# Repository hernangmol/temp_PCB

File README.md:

# temp_PCB
Repositorio temporal de diseños PCB propios

Carpeta SMTB:

Contiene el trabajo "Sistema de monitoreo térmico de bogies", realizado en el marco de la Especialización en Sistemas Embebidos (FIUBA) para Trenes Argentinos Operaciones.
Se trata de un desarrollo para sustitución de importación de un sistema incluido en el equipamiento original de las locomotoras CNR - CKD 8G/H.
(Ver repositorio github/hernangmol/SMTB.git)

Carpeta Barra_cortocircuito:

Se trata del desarrollo realizado en CENADIF de una barra de cortocircuito para tercer riel. La misma mantiene la condición segura mientras se realizan tareas de mantenimiento de tercer riel.
Incorpora además un detector de tensión y luces de aviso de riel energizado.

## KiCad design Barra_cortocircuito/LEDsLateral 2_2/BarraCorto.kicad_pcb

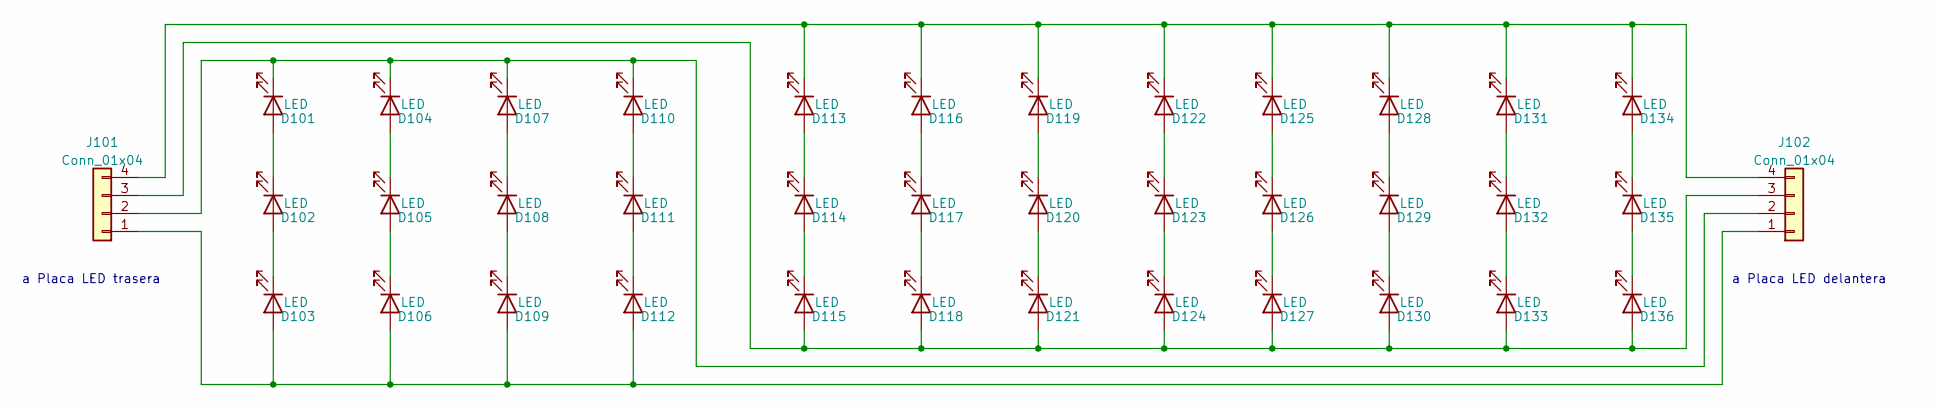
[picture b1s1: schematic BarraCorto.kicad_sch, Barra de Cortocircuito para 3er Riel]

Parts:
D101, D102, D103, D104, D105, D106, D107, D108, D109, D110, D111, D112, D113, D114, D115, D116, D117, D118, D119, D120, D121, D122, D123, D124, D125, D126, D127, D128, D129, D130, D131, D132, D133, D134, D135, D136: LED; LED_PLCC_2835
J101, J102: Conn_01x04; molex_EDGELOCK_4-CKT_Mod

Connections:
unnamed: D101.1 (K), D104.1 (K), D107.1 (K), D110.1 (K), J101.2, J102.2
unnamed: D101.2 (A), D102.1 (K)
unnamed: D102.2 (A), D103.1 (K)
unnamed: D103.2 (A), D106.2 (A), D109.2 (A), D112.2 (A), J101.1, J102.1
unnamed: D104.2 (A), D105.1 (K)
unnamed: D105.2 (A), D106.1 (K)
unnamed: D107.2 (A), D108.1 (K)
unnamed: D108.2 (A), D109.1 (K)
unnamed: D110.2 (A), D111.1 (K)
unnamed: D111.2 (A), D112.1 (K)
unnamed: D113.1 (K), D116.1 (K), D119.1 (K), D122.1 (K), D125.1 (K), D128.1 (K), D131.1 (K), D134.1 (K), J101.4, J102.4
unnamed: D113.2 (A), D114.1 (K)
unnamed: D114.2 (A), D115.1 (K)
unnamed: D115.2 (A), D118.2 (A), D121.2 (A), D124.2 (A), D127.2 (A), D130.2 (A), D133.2 (A), D136.2 (A), J101.3, J102.3
unnamed: D116.2 (A), D117.1 (K)
unnamed: D117.2 (A), D118.1 (K)
unnamed: D119.2 (A), D120.1 (K)
unnamed: D120.2 (A), D121.1 (K)
unnamed: D122.2 (A), D123.1 (K)
unnamed: D123.2 (A), D124.1 (K)
unnamed: D125.2 (A), D126.1 (K)
unnamed: D126.2 (A), D127.1 (K)
unnamed: D128.2 (A), D129.1 (K)
unnamed: D129.2 (A), D130.1 (K)
unnamed: D131.2 (A), D132.1 (K)
unnamed: D132.2 (A), D133.1 (K)
unnamed: D134.2 (A), D135.1 (K)
unnamed: D135.2 (A), D136.1 (K)

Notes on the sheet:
a Placa LED delantera
a Placa LED trasera

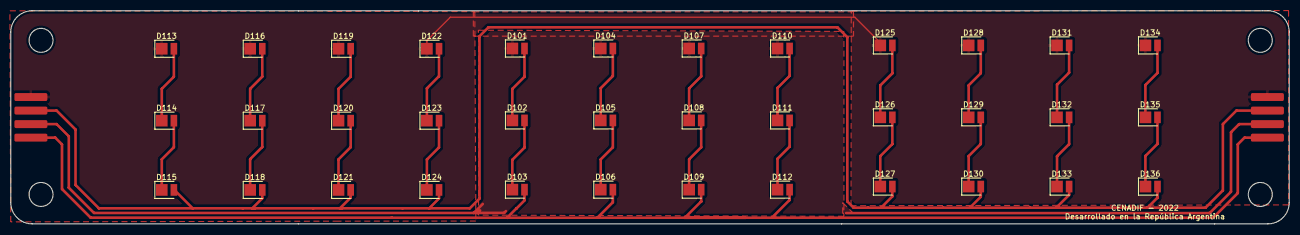
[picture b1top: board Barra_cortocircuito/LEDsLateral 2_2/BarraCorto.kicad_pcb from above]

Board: 2 copper layers, 240.0 x 40.0 mm, 38 parts (0 on the bottom side), 28 nets.

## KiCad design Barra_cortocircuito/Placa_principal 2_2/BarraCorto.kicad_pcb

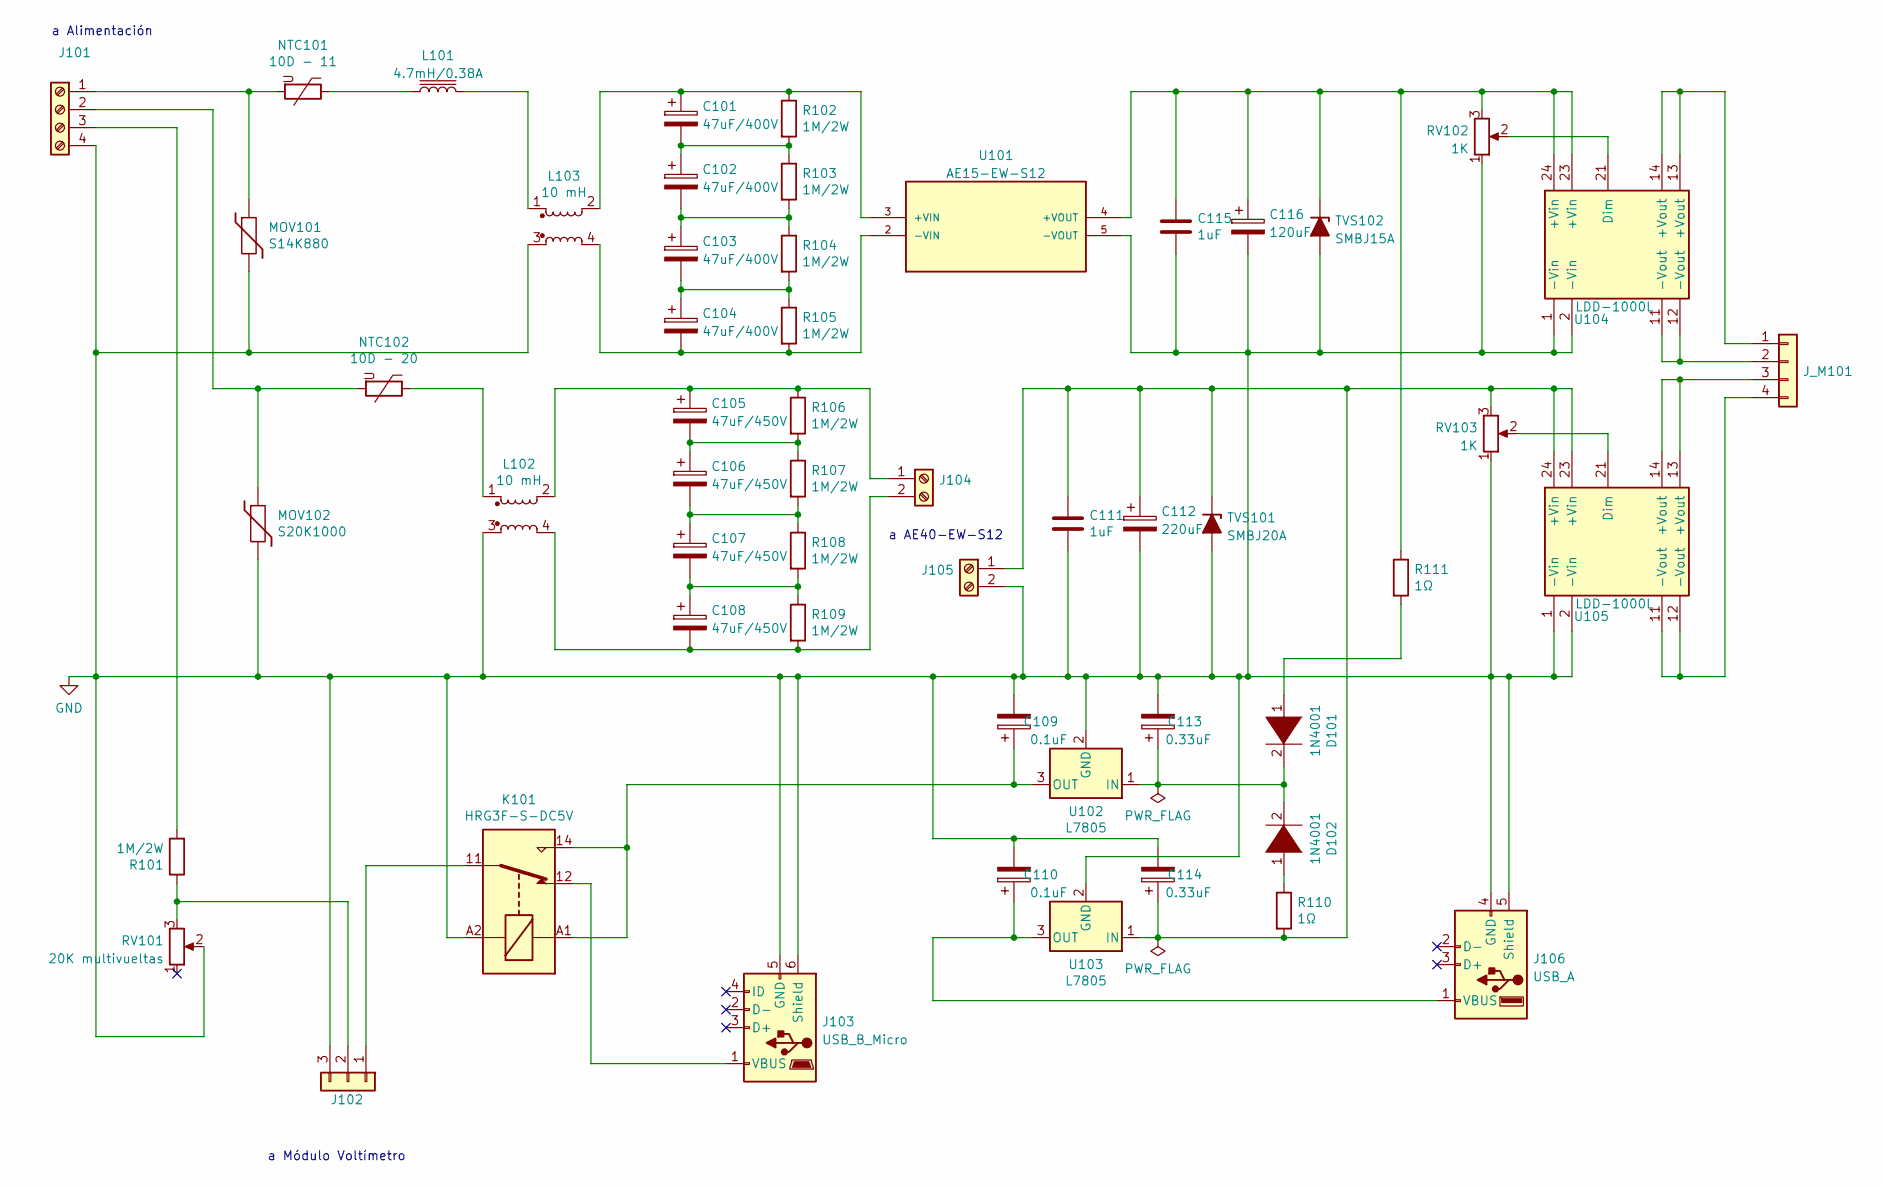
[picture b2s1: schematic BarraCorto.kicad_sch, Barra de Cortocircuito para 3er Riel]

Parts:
C101, C102, C103, C104: 47uF/400V; CP_Radial_D18.0mm_P7.50mm
C105, C106, C107, C108: 47uF/450V; CP_Radial_D18.0mm_P7.50mm
C109, C110: 0.1uF; CP_Radial_D8.0mm_P5.00mm
C111, C115: 1uF; C_Disc_D8.0mm_W2.5mm_P5.00mm
C112: 220uF; CP_Radial_D18.0mm_P7.50mm
C113, C114: 0.33uF; CP_Radial_D8.0mm_P5.00mm
C116: 120uF; CP_Radial_D18.0mm_P7.50mm
D101, D102: 1N4001; D_DO-41_SOD81_P10.16mm_Horizontal
J101: Bornera_Tornillo_01x04; TerminalBlock_bornier-4_P5.08mm
J102: Conn_01x03; Molex_KK-254_AE-6410-03A_1x03_P2.54mm_Vertical
J103: USB_B_Micro; PinHeader_1x06_P2.54mm_Vertical
J104, J105: BorneraTornillo_01x02; TerminalBlock_bornier-2_P5.08mm
J106: USB_A; USB_A_Molex_67643_Horizontal
J_M101: Conn_01x04; Molex_KK-254_AE-6410-04A_1x04_P2.54mm_Vertical
K101: HRG3F-S-DC5V
L101: 4.7mH/0.38A; L_Radial_D27.9mm_P19.05mm_Vishay_IHB-3
L102, L103: 10 mH
MOV101: S14K880; RV_Disc_D15.5mm_W11mm_P7.5mm
MOV102: S20K1000; RV_Disc_D21.5mm_W11.4mm_P10mm
NTC101: 10D - 11; RV_Disc_D12mm_W7.9mm_P7.5mm
NTC102: 10D - 20; RV_Disc_D21.5mm_W7.1mm_P10mm
R101, R102, R103, R104, R105, R106, R107, R108, R109: 1M/2W; R_Axial_DIN0516_L15.5mm_D5.0mm_P20.32mm_Horizontal
R110, R111: 1Ω; R_Axial_DIN0516_L15.5mm_D5.0mm_P20.32mm_Horizontal
RV101: 20K multivueltas; Potentiometer_Bourns_3296W_Vertical
RV102, RV103: 1K; Potentiometer_Bourns_3296W_Vertical
TVS101: SMBJ20A; D_SMB
TVS102: SMBJ15A; D_SMB
U101: AE15-EW-S12; AE15_EW_S12; PARTREV 1.0
U102, U103: L7805; TO-220-3_Horizontal_TabDown
U104, U105: LDD-1000L

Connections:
GND: C109.2, C110.2, C111.2, C112.2, C113.2, C114.2, C115.2, C116.2, J101.4, J102.3, J103.5 (GND), J103.6 (Shield), J105.2, J106.4 (GND), J106.5 (Shield), K101.A2, L102.3, L103.3, MOV101.2, MOV102.2, RV101.2, RV102.1, RV103.1, TVS101.2 (A), TVS102.2 (A), U101.5 (-VOUT), U102.2 (GND), U103.2 (GND), U104.1 (-Vin), U104.2 (-Vin), U105.1 (-Vin), U105.2 (-Vin)
unnamed: C101.1, L103.2, R102.1, U101.3 (+VIN)
unnamed: C101.2, C102.1, R102.2, R103.1
unnamed: C102.2, C103.1, R103.2, R104.1
unnamed: C103.2, C104.1, R104.2, R105.1
unnamed: C104.2, L103.4, R105.2, U101.2 (-VIN)
unnamed: C105.1, J104.1, L102.2, R106.1
unnamed: C105.2, C106.1, R106.2, R107.1
unnamed: C106.2, C107.1, R107.2, R108.1
unnamed: C107.2, C108.1, R108.2, R109.1
unnamed: C108.2, J104.2, L102.4, R109.2
unnamed: C109.1, K101.14, K101.A1, U102.3 (OUT)
unnamed: C110.1, J106.1 (VBUS), U103.3 (OUT)
unnamed: C111.1, C112.1, C114.1, J105.1, R110.2, RV103.3, TVS101.1 (K), U103.1 (IN), U105.23 (+Vin), U105.24 (+Vin)
unnamed: C113.1, D101.2 (A), D102.2 (A), U102.1 (IN)
unnamed: C115.1, C116.1, R111.1, RV102.3, TVS102.1 (K), U101.4 (+VOUT), U104.23 (+Vin), U104.24 (+Vin)
unnamed: D101.1 (K), R111.2
unnamed: D102.1 (K), R110.1
unnamed: J101.1, MOV101.1, NTC101.2
unnamed: J101.2, MOV102.1, NTC102.2
unnamed: J101.3, R101.2
unnamed: J102.1, K101.11
unnamed: J102.2, R101.1, RV101.3
unnamed: J103.1 (VBUS), K101.12
unnamed: J_M101.1, U104.13 (+Vout), U104.14 (+Vout)
unnamed: J_M101.2, U104.11 (-Vout), U104.12 (-Vout)
unnamed: J_M101.3, U105.13 (+Vout), U105.14 (+Vout)
unnamed: J_M101.4, U105.11 (-Vout), U105.12 (-Vout)
unnamed: L101.1, NTC101.1
unnamed: L101.2, L103.1
unnamed: L102.1, NTC102.1
unnamed: RV102.2, U104.21 (Dim)
unnamed: RV103.2, U105.21 (Dim)

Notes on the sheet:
a AE40-EW-S12
a Módulo Voltímetro
a Alimentación

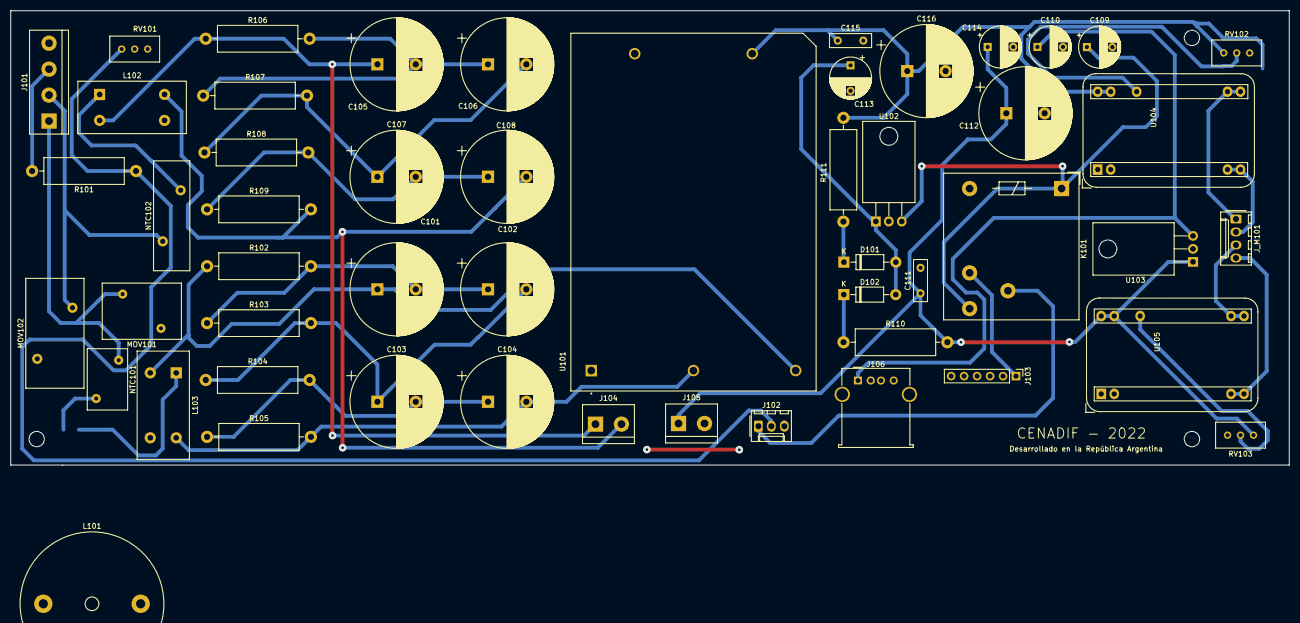
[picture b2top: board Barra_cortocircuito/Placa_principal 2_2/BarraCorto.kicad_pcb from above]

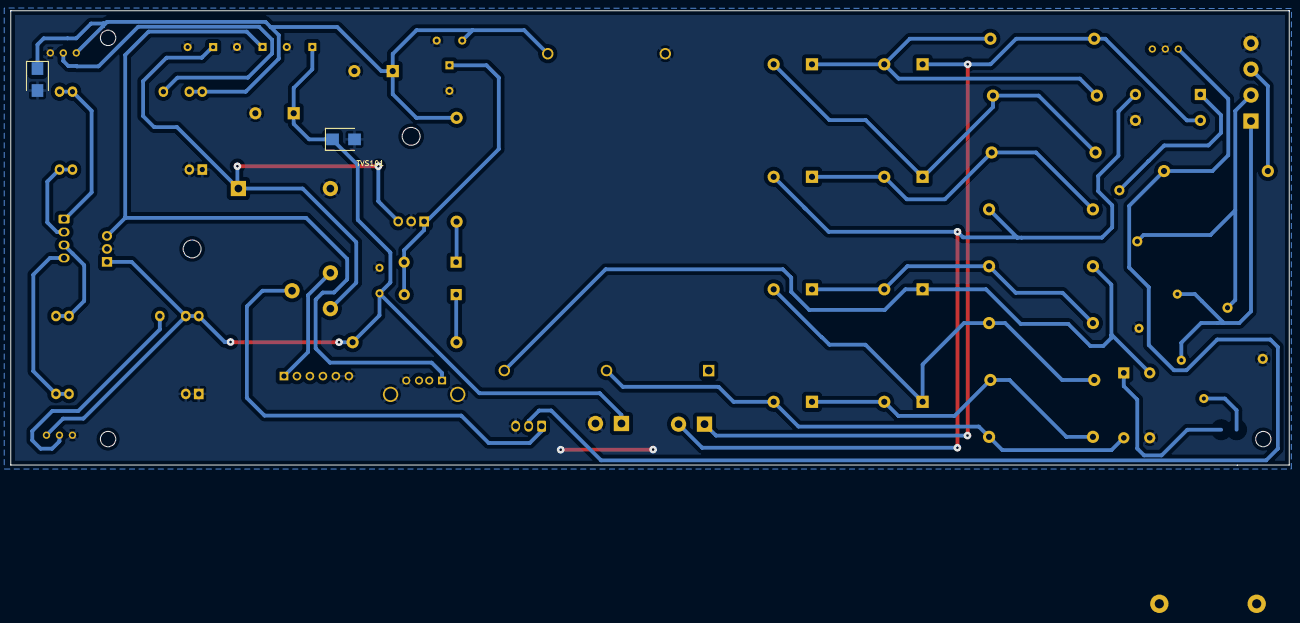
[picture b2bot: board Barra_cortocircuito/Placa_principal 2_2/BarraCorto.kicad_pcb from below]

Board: 2 copper layers, 250.2 x 88.9 mm, 54 parts (2 on the bottom side), 33 nets.

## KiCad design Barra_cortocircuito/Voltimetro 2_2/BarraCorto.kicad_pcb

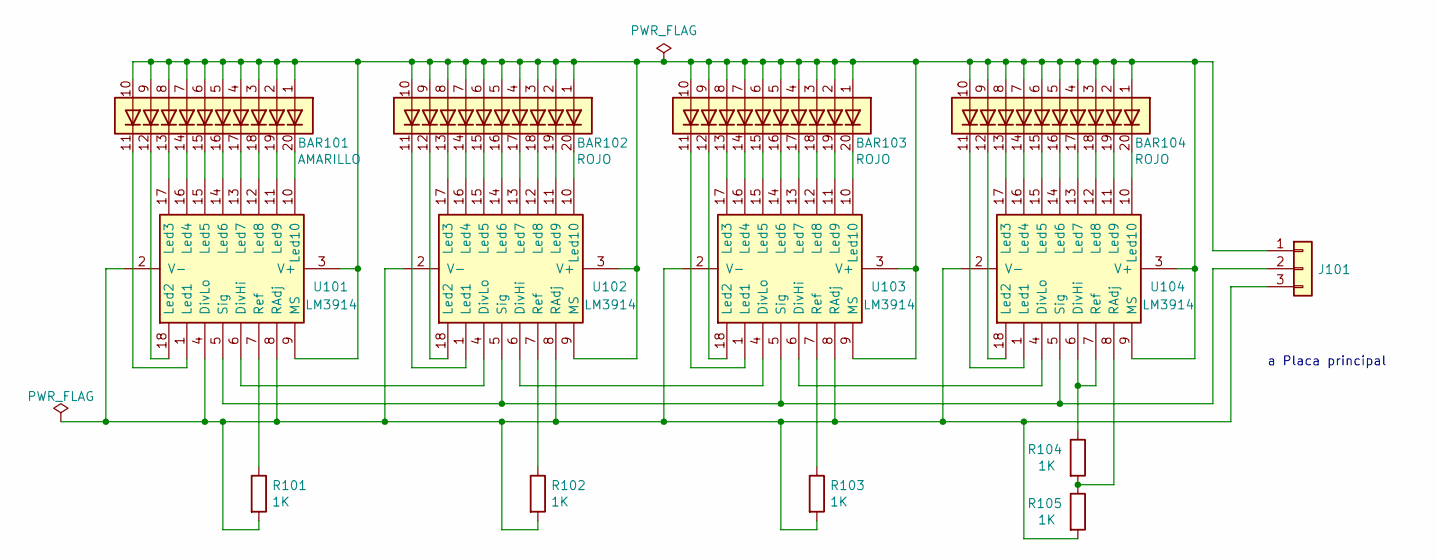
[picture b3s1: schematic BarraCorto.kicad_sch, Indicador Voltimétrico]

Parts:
BAR101: AMARILLO; HDSP-4830
BAR102, BAR103, BAR104: ROJO; HDSP-4830
J101: Conn_01x03; Molex_KK-254_AE-6410-03A_1x03_P2.54mm_Vertical
R101, R102, R103, R104, R105: 1K; R_Axial_DIN0207_L6.3mm_D2.5mm_P10.16mm_Horizontal
U101, U102, U103, U104: LM3914; DIP-18_W7.62mm_Socket

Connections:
unnamed: BAR101.1 (A), BAR101.2 (A), BAR101.3 (A), BAR101.4 (A), BAR101.5 (A), BAR101.6 (A), BAR101.7 (A), BAR101.8 (A), BAR101.9 (A), BAR101.10 (A), BAR102.1 (A), BAR102.2 (A), BAR102.3 (A), BAR102.4 (A), BAR102.5 (A), BAR102.6 (A), BAR102.7 (A), BAR102.8 (A), BAR102.9 (A), BAR102.10 (A), BAR103.1 (A), BAR103.2 (A), BAR103.3 (A), BAR103.4 (A), BAR103.5 (A), BAR103.6 (A), BAR103.7 (A), BAR103.8 (A), BAR103.9 (A), BAR103.10 (A), BAR104.1 (A), BAR104.2 (A), BAR104.3 (A), BAR104.4 (A), BAR104.5 (A), BAR104.6 (A), BAR104.7 (A), BAR104.8 (A), BAR104.9 (A), BAR104.10 (A), J101.1, U101.3 (V+), U101.9 (MS), U102.3 (V+), U102.9 (MS), U103.3 (V+), U103.9 (MS), U104.3 (V+), U104.9 (MS)
unnamed: BAR101.11 (K), U101.1 (Led1)
unnamed: BAR101.12 (K), U101.18 (Led2)
unnamed: BAR101.13 (K), U101.17 (Led3)
unnamed: BAR101.14 (K), U101.16 (Led4)
unnamed: BAR101.15 (K), U101.15 (Led5)
unnamed: BAR101.16 (K), U101.14 (Led6)
unnamed: BAR101.17 (K), U101.13 (Led7)
unnamed: BAR101.18 (K), U101.12 (Led8)
unnamed: BAR101.19 (K), U101.11 (Led9)
unnamed: BAR101.20 (K), U101.10 (Led10)
unnamed: BAR102.11 (K), U102.1 (Led1)
unnamed: BAR102.12 (K), U102.18 (Led2)
unnamed: BAR102.13 (K), U102.17 (Led3)
unnamed: BAR102.14 (K), U102.16 (Led4)
unnamed: BAR102.15 (K), U102.15 (Led5)
unnamed: BAR102.16 (K), U102.14 (Led6)
unnamed: BAR102.17 (K), U102.13 (Led7)
unnamed: BAR102.18 (K), U102.12 (Led8)
unnamed: BAR102.19 (K), U102.11 (Led9)
unnamed: BAR102.20 (K), U102.10 (Led10)
unnamed: BAR103.11 (K), U103.1 (Led1)
unnamed: BAR103.12 (K), U103.18 (Led2)
unnamed: BAR103.13 (K), U103.17 (Led3)
unnamed: BAR103.14 (K), U103.16 (Led4)
unnamed: BAR103.15 (K), U103.15 (Led5)
unnamed: BAR103.16 (K), U103.14 (Led6)
unnamed: BAR103.17 (K), U103.13 (Led7)
unnamed: BAR103.18 (K), U103.12 (Led8)
unnamed: BAR103.19 (K), U103.11 (Led9)
unnamed: BAR103.20 (K), U103.10 (Led10)
unnamed: BAR104.11 (K), U104.1 (Led1)
unnamed: BAR104.12 (K), U104.18 (Led2)
unnamed: BAR104.13 (K), U104.17 (Led3)
unnamed: BAR104.14 (K), U104.16 (Led4)
unnamed: BAR104.15 (K), U104.15 (Led5)
unnamed: BAR104.16 (K), U104.14 (Led6)
unnamed: BAR104.17 (K), U104.13 (Led7)
unnamed: BAR104.18 (K), U104.12 (Led8)
unnamed: BAR104.19 (K), U104.11 (Led9)
unnamed: BAR104.20 (K), U104.10 (Led10)
unnamed: J101.2, U101.5 (Sig), U102.5 (Sig), U103.5 (Sig), U104.5 (Sig)
unnamed: J101.3, R101.2, R102.2, R103.2, R105.2, U101.2 (V-), U101.4 (DivLo), U101.8 (RAdj), U102.2 (V-), U102.8 (RAdj), U103.2 (V-), U103.8 (RAdj), U104.2 (V-)
unnamed: R101.1, U101.7 (Ref)
unnamed: R102.1, U102.7 (Ref)
unnamed: R103.1, U103.7 (Ref)
unnamed: R104.1, U104.6 (DivHi), U104.7 (Ref)
unnamed: R104.2, R105.1, U104.8 (RAdj)
unnamed: U101.6 (DivHi), U102.4 (DivLo)
unnamed: U102.6 (DivHi), U103.4 (DivLo)
unnamed: U103.6 (DivHi), U104.4 (DivLo)

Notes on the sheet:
a Placa principal

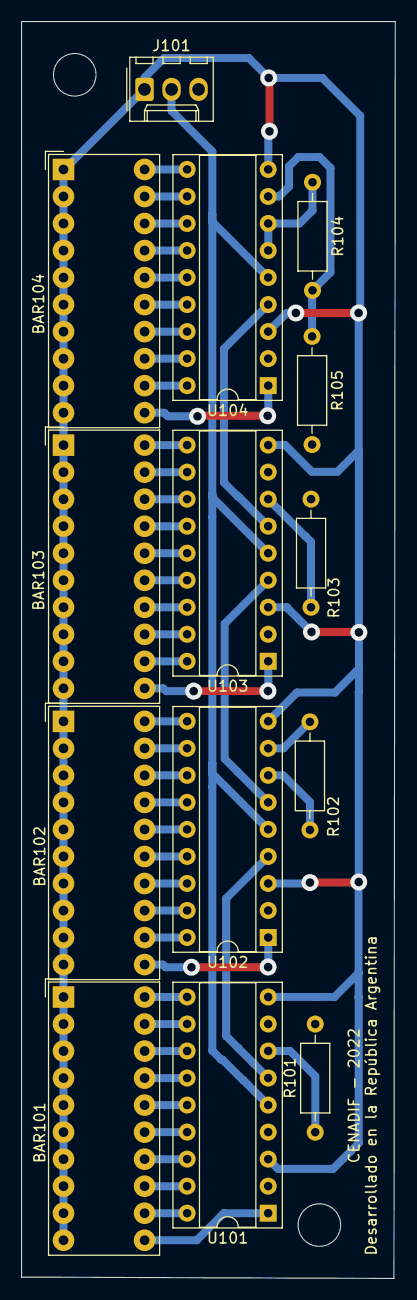
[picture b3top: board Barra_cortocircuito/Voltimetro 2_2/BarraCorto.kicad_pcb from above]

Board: 2 copper layers, 35.1 x 118.1 mm, 14 parts (0 on the bottom side), 51 nets.

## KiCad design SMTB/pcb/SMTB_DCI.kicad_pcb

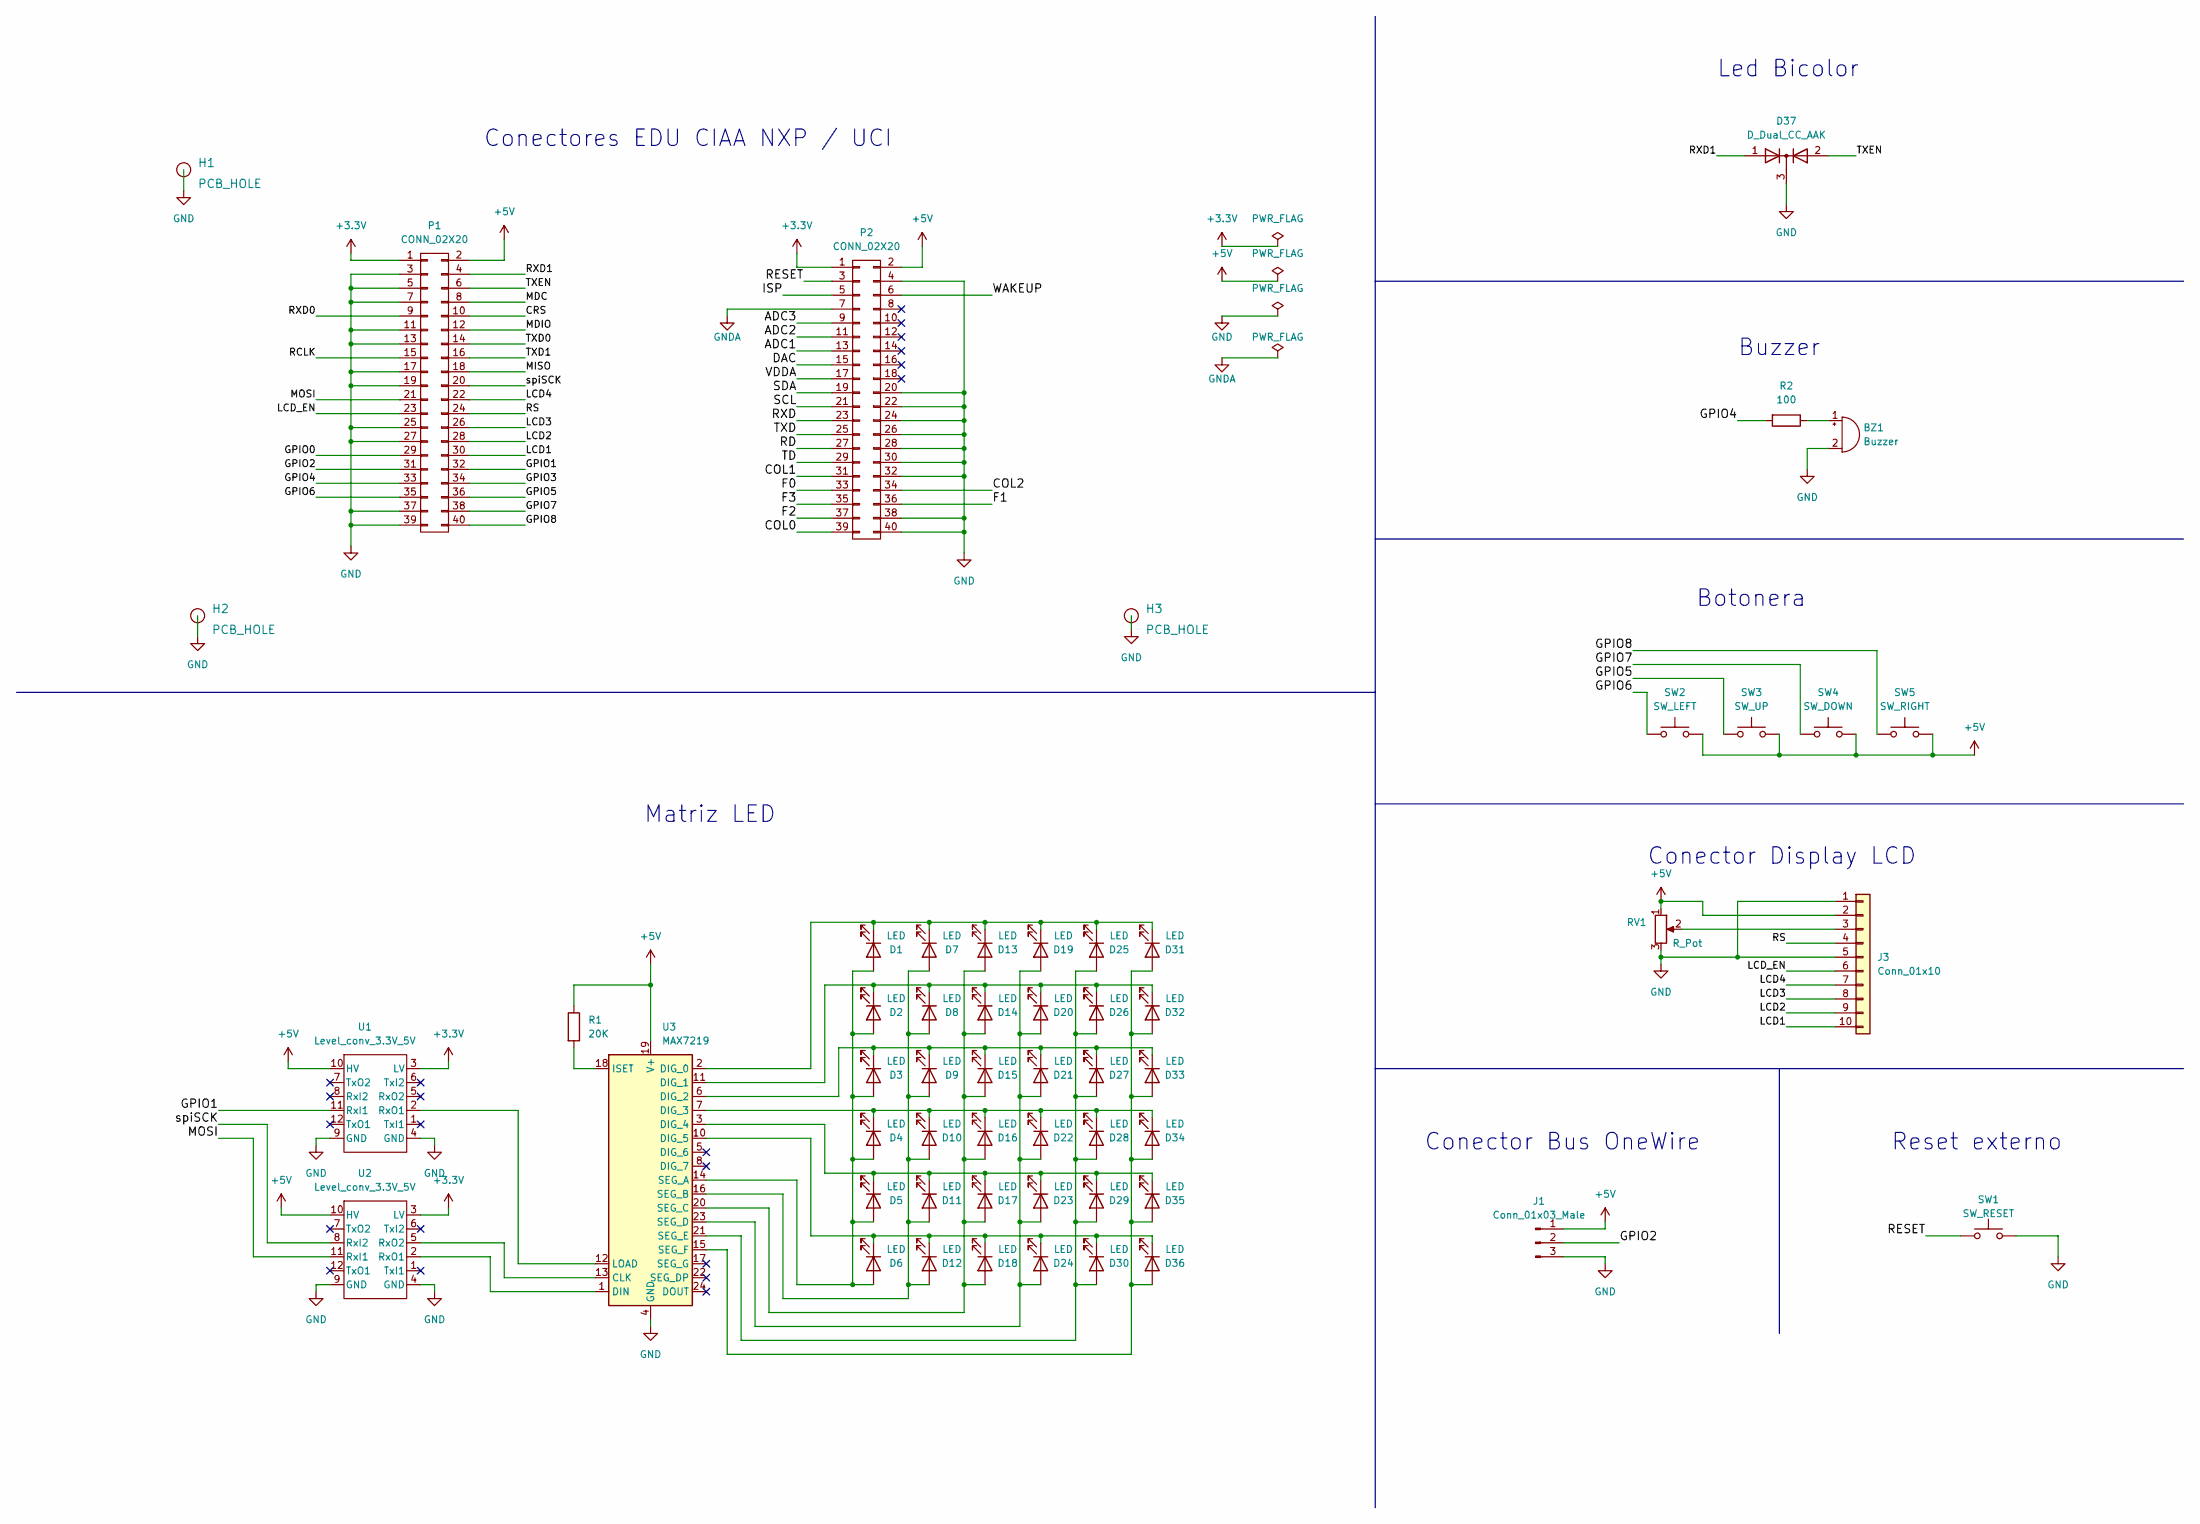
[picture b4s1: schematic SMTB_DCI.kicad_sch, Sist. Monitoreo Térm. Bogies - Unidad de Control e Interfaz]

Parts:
BZ1: Buzzer; Buzzer_12x9.5RM7.6
D1, D2, D3, D4, D5, D6, D7, D8, D9, D10, D11, D12, D13, D14, D15, D16, D17, D18, D19, D20, D21, D22, D23, D24, D25, D26, D27, D28, D29, D30, D31, D32, D33, D34, D35, D36: LED; LED_D5.0mm
D37: D_Dual_CC_AAK; LED_D5.0mm-3
H1: PCB_HOLE
H2, H3: PCB_HOLE; MountingHole_4.3mm_M4_ISO14580_Pad_TopBottom
J1: Conn_01x03_Male; Molex_KK-254_AE-6410-03A_1x03_P2.54mm_Vertical
J3: Conn_01x10; Molex_KK-254_AE-6410-10A_1x10_P2.54mm_Vertical
P1, P2: CONN_02X20; PinHeader_2x20_P2.54mm_Vertical
R1: 20K; R_Axial_DIN0207_L6.3mm_D2.5mm_P10.16mm_Horizontal
R2: 100; R_Axial_DIN0207_L6.3mm_D2.5mm_P10.16mm_Horizontal
RV1: R_Pot; Potentiometer_Bourns_3296W_Vertical
SW1: SW_RESET; SW_PUSH_6mm
SW2: SW_LEFT; SW_PUSH_6mm
SW3: SW_UP; SW_PUSH_6mm
SW4: SW_DOWN; SW_PUSH_6mm
SW5: SW_RIGHT; SW_PUSH_6mm
U1, U2: Level_conv_3.3V_5V; Conv_DCDC
U3: MAX7219; DIP-24_W7.62mm

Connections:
+3.3V: P1.1, P2.1, U1.3 (LV), U2.3 (LV)
+5V: J1.1, J3.2, P1.2, P2.2, R1.1, RV1.1, SW2.2, SW3.2, SW4.2, SW5.2, U1.10 (HV), U2.10 (HV), U3.19 (V+)
/ADC1: P2.13
/ADC2: P2.11
/ADC3: P2.9
/COL0: P2.39
/COL1: P2.31
/COL2: P2.34
/CRS: P1.10
/DAC: P2.15
/F0: P2.33
/F1: P2.36
/F2: P2.37
/F3: P2.35
/GPIO0: P1.29
/GPIO1: P1.32, U1.11 (RxI1)
/GPIO2: J1.2, P1.31
/GPIO3: P1.34
/GPIO4: P1.33, R2.2
/GPIO5: P1.36, SW3.1
/GPIO6: P1.35, SW2.1
/GPIO7: P1.38, SW4.1
/GPIO8: P1.40, SW5.1
/ISP: P2.5
/LCD1: J3.10, P1.30
/LCD2: J3.9, P1.28
/LCD3: J3.8, P1.26
/LCD4: J3.7, P1.22
/LCD_EN: J3.6, P1.23
/MDC: P1.8
/MDIO: P1.12
/MISO: P1.18
/MOSI: P1.21, U2.11 (RxI1)
/RCLK: P1.15
/RD: P2.27
/RESET: P2.3, SW1.1
/RS: J3.4, P1.24
/RXD: P2.23
/RXD0: P1.9
/RXD1: D37.1 (A), P1.4
/SCL: P2.21
/SDA: P2.19
/TD: P2.29
/TXD: P2.25
/TXD0: P1.14
/TXD1: P1.16
/TXEN: D37.2 (A), P1.6
/VDDA: P2.17
/WAKEUP: P2.6
/spiSCK: P1.20, U2.8 (RxI2)
GND: BZ1.2 (+), D37.3 (K), H1.1, H2.1, H3.1, J1.3, J3.1, J3.5, P1.3, P1.5, P1.7, P1.11, P1.13, P1.17, P1.19, P1.25, P1.27, P1.37, P1.39, P2.4, P2.20, P2.22, P2.24, P2.26, P2.28, P2.30, P2.32, P2.38, P2.40, RV1.3, SW1.2, U1.4 (GND), U1.9 (GND), U2.4 (GND), U2.9 (GND), U3.4 (GND), U3.9 (GND)
GNDA: P2.7
unnamed: BZ1.1 (-), R2.1
unnamed: D1.1 (K), D7.1 (K), D13.1 (K), D19.1 (K), D25.1 (K), D31.1 (K), U3.2 (DIG_0)
unnamed: D1.2 (A), D2.2 (A), D3.2 (A), D4.2 (A), D5.2 (A), D6.2 (A), U3.14 (SEG_A)
unnamed: D4.1 (K), D10.1 (K), D16.1 (K), D22.1 (K), D28.1 (K), D34.1 (K), U3.7 (DIG_3)
unnamed: D7.2 (A), D8.2 (A), D9.2 (A), D10.2 (A), D11.2 (A), D12.2 (A), U3.16 (SEG_B)
unnamed: D5.1 (K), D11.1 (K), D17.1 (K), D23.1 (K), D29.1 (K), D35.1 (K), U3.3 (DIG_4)
unnamed: D6.1 (K), D12.1 (K), D18.1 (K), D24.1 (K), D30.1 (K), D36.1 (K), U3.10 (DIG_5)
unnamed: D13.2 (A), D14.2 (A), D15.2 (A), D16.2 (A), D17.2 (A), D18.2 (A), U3.20 (SEG_C)
unnamed: D2.1 (K), D8.1 (K), D14.1 (K), D20.1 (K), D26.1 (K), D32.1 (K), U3.11 (DIG_1)
unnamed: D3.1 (K), D9.1 (K), D15.1 (K), D21.1 (K), D27.1 (K), D33.1 (K), U3.6 (DIG_2)
unnamed: D19.2 (A), D20.2 (A), D21.2 (A), D22.2 (A), D23.2 (A), D24.2 (A), U3.23 (SEG_D)
unnamed: D25.2 (A), D26.2 (A), D27.2 (A), D28.2 (A), D29.2 (A), D30.2 (A), U3.21 (SEG_E)
unnamed: D31.2 (A), D32.2 (A), D33.2 (A), D34.2 (A), D35.2 (A), D36.2 (A), U3.15 (SEG_F)
unnamed: J3.3, RV1.2
unnamed: R1.2, U3.18 (ISET)
unnamed: U1.2 (RxO1), U3.12 (LOAD)
unnamed: U2.2 (RxO1), U3.1 (DIN)
unnamed: U2.5 (RxO2), U3.13 (CLK)

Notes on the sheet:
Conector Display LCD
Conector Bus OneWire
Conectores EDU CIAA NXP / UCI
Botonera
Led Bicolor
Reset externo
Buzzer
Matriz LED

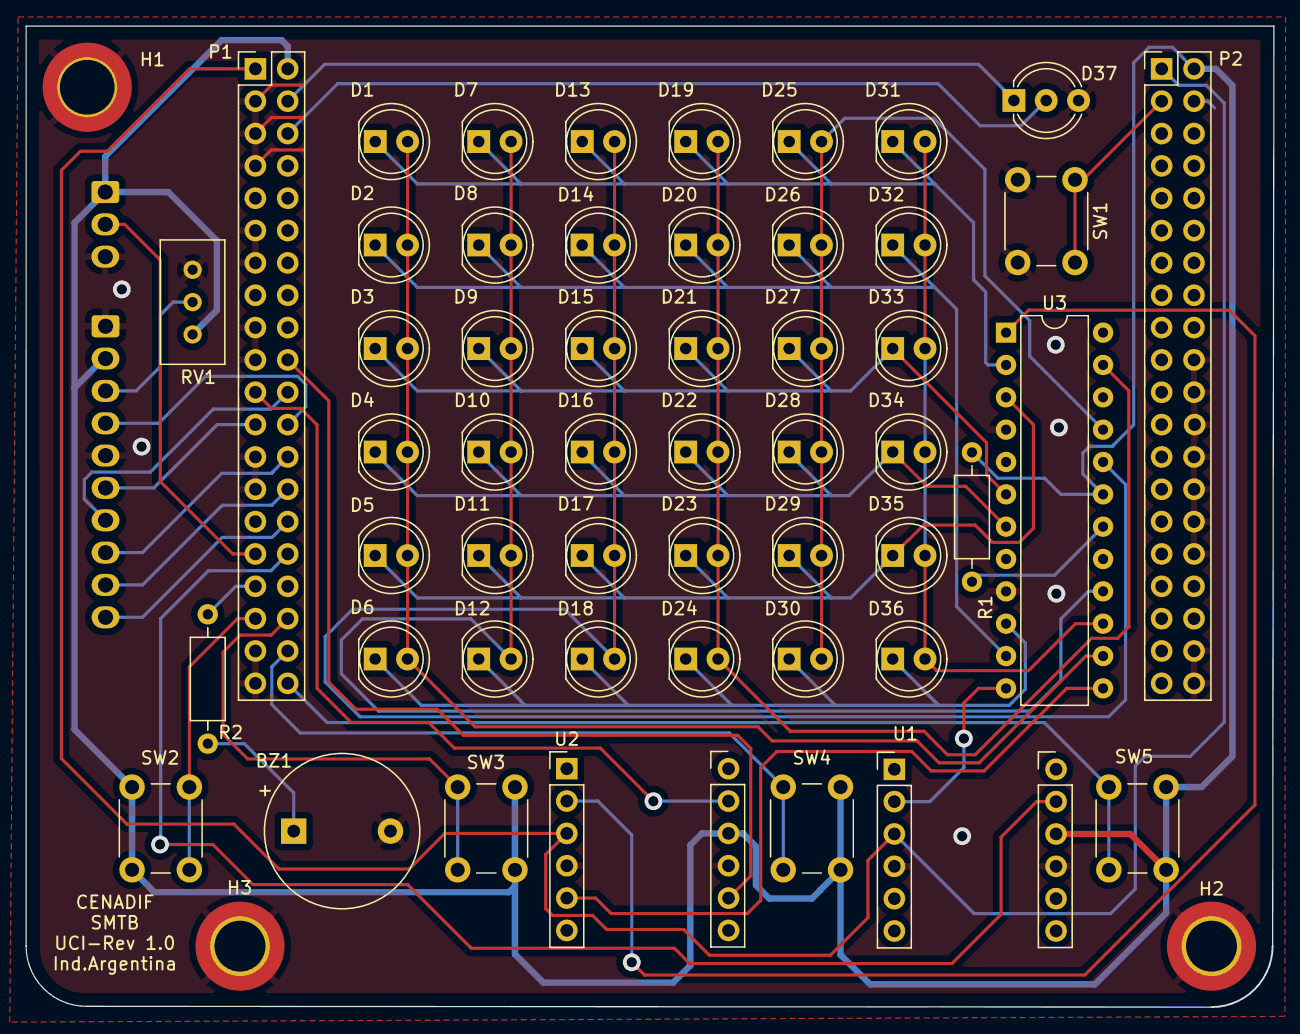
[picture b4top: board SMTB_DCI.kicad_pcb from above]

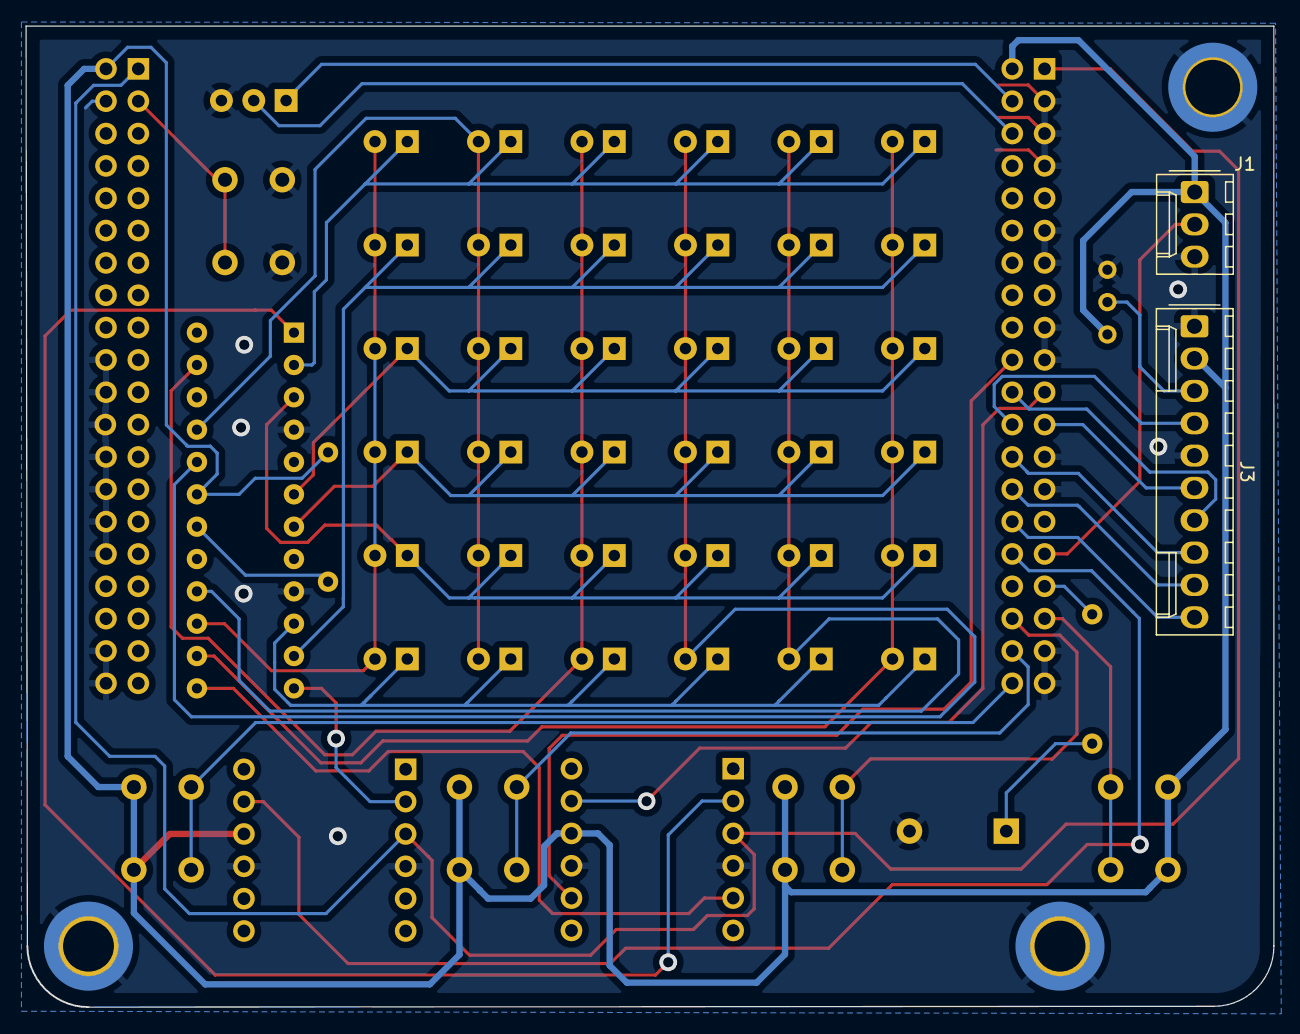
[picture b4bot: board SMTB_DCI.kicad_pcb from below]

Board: 2 copper layers, 98.0 x 77.1 mm, 56 parts (2 on the bottom side), 39 nets.

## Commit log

2024-01-17 Commit inicial
2024-01-17 actualizacion README.md

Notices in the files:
SMTB/pcb/SMTB_DCI.kicad_pcb:
CC BY 4.0
